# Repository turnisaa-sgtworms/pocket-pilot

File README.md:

epic tiny keeb, so cool.

fits in the 100mm x 100mm jlcpcb coupon requirements! i ordered mine for 12 usd (with tarriffs!)

sub minimum choc spacing - you will have to sacrifice 22x choc switches to sand/file the sides down. you'll also need to 3d print some keycaps (idk if something like the MNT pocket reform keycaps will fit.) my files are included.

more info to come!

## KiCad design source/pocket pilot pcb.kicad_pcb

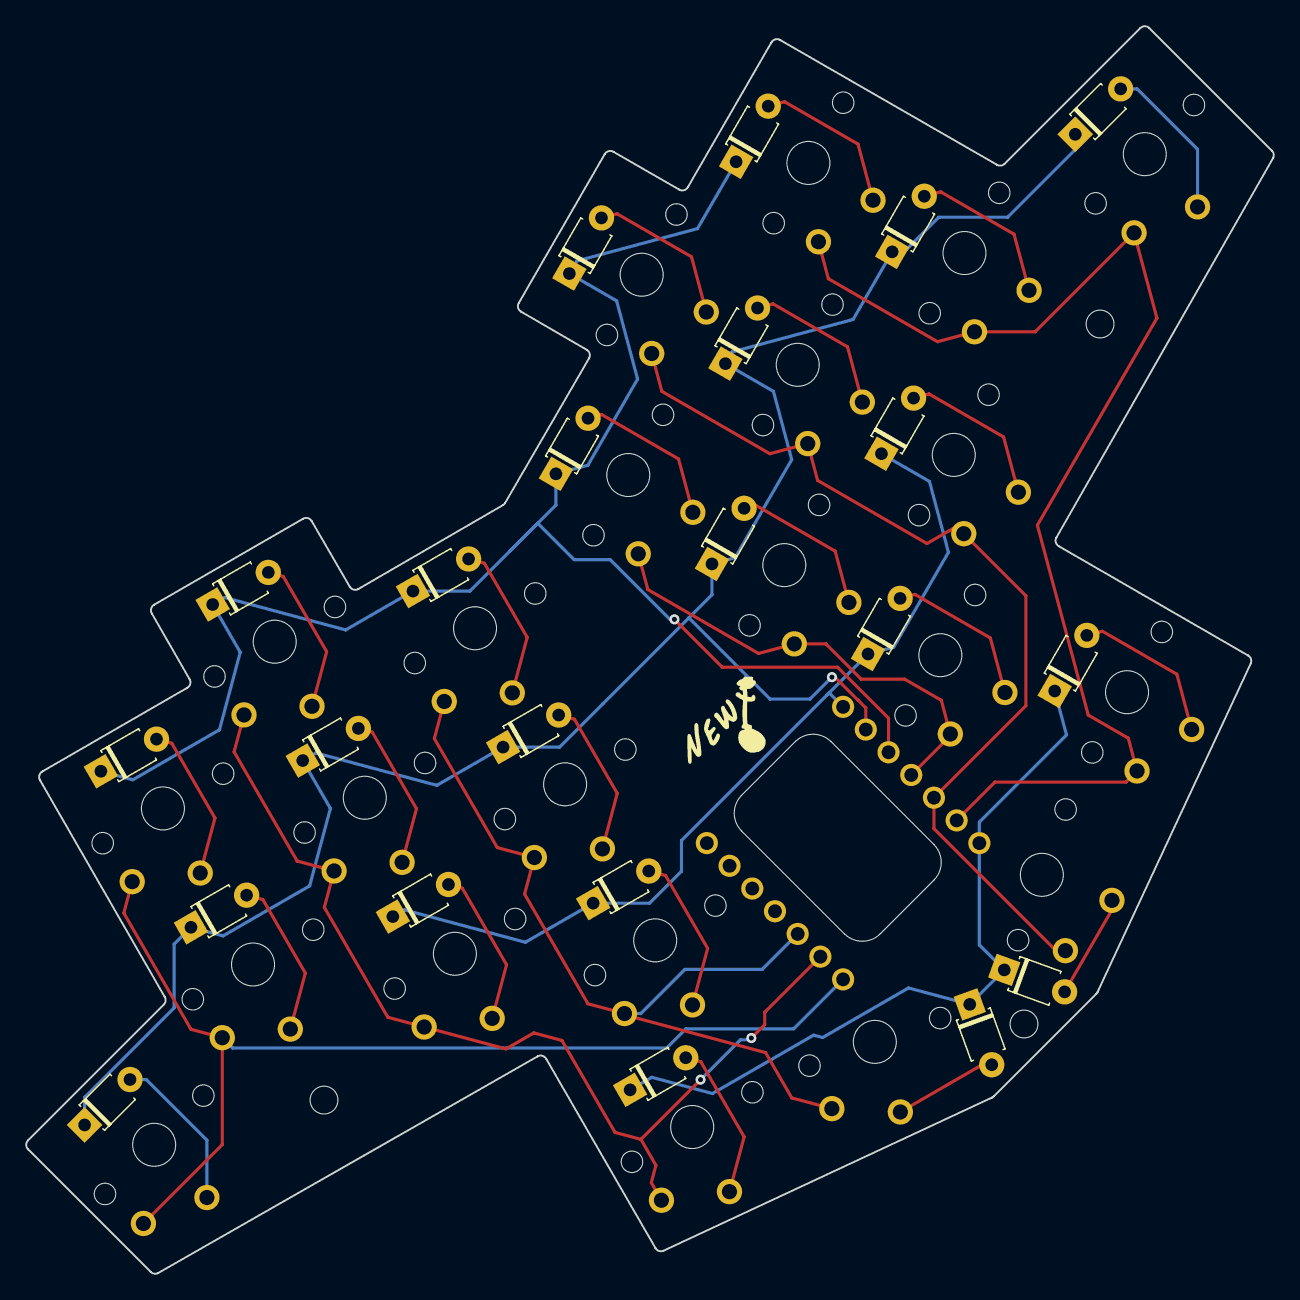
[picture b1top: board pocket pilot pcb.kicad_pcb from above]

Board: 2 copper layers, 98.7 x 98.7 mm, 45 parts (1 on the bottom side), 32 nets.

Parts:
D1, D2, D3, D4, D5, D6, D7, D8, D9, D10, D11, D12, D13, D14, D15, D16, D17, D18, D19, D20, D21, D22: 5mm diode
MCU1: ProMicro
S1, S2, S3, S4, S5, S6, S7, S8, S9, S10, S11, S12, S13, S14, S15, S16, S17, S18, S19, S20, S21, S22: SW_choc_no_silk

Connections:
P6: MCU1.21, S18.1, S19.1, S20.1
P7: MCU1.22, S15.1, S16.1, S17.1, S22.1
P8: MCU1.23, S12.1, S13.1, S14.1, S21.1
P9: D10.1, D11.1, D21.1, D22.1, MCU1.24
P10: MCU1.12, S1.1, S2.1, S3.1
P14: MCU1.10, S7.1, S8.1, S9.1, S11.1
P16: MCU1.11, S4.1, S5.1, S6.1, S10.1
P18: D3.1, D6.1, D9.1, D14.1, D17.1, D20.1, MCU1.8
P19: D1.1, D2.1, D5.1, D8.1, D12.1, D13.1, D16.1, D19.1, MCU1.7
P20: D4.1, D7.1, D15.1, D18.1, MCU1.6
home_thumb: D11.2, S11.2
index_bottom: D7.2, S7.2
index_home: D8.2, S8.2
index_top: D9.2, S9.2
middle_bottom: D4.2, S4.2
middle_home: D5.2, S5.2
middle_top: D6.2, S6.2
mirror_home_thumb: D22.2, S22.2
mirror_index_bottom: D18.2, S18.2
mirror_index_home: D19.2, S19.2
mirror_index_top: D20.2, S20.2
mirror_middle_bottom: D15.2, S15.2
mirror_middle_home: D16.2, S16.2
mirror_middle_top: D17.2, S17.2
mirror_near_thumb: D21.2, S21.2
mirror_pinky_home: D12.2, S12.2
mirror_ring_home: D13.2, S13.2
mirror_ring_top: D14.2, S14.2
near_thumb: D10.2, S10.2
pinky_home: D1.2, S1.2
ring_home: D2.2, S2.2
ring_top: D3.2, S3.2

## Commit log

2025-06-26 epic and swag initial commit
2025-07-06 added keycaps
